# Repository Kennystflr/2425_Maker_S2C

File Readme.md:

# Sprinter Coffee Cell

Mission : Deliver Warm Coffee to the Technician on the ground level from first floor

The system includes :
- A fast RC car with a lot of cool features (might turn autonomous)
- A Lifter module.

This is a uninversitary project developed in the Maker Option at ENSEA (France).

Developed by Kenny Saint Fleur

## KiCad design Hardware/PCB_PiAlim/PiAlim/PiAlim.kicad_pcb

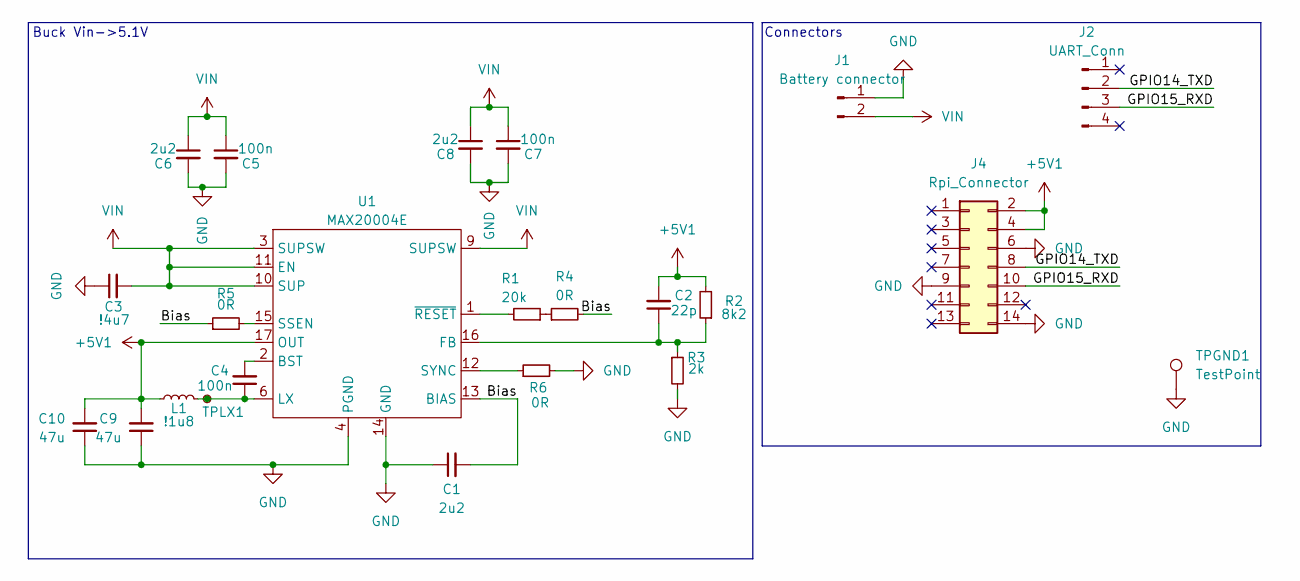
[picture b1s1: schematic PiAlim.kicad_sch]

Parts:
C1, C6, C8: 2u2; C_0805_2012Metric
C2: 22p; C_0402_1005Metric
C3: !4u7; C_0805_2012Metric; MPN UMK212BBJ475KG-T
C4, C5, C7: 100n; C_0402_1005Metric
C9, C10: 47u; C_0805_2012Metric
J1: Battery connector; AMASS_XT60-F_1x02_P7.20mm_Vertical
J2: UART_Conn; JST_XH_B4B-XH-A_1x04_P2.50mm_Vertical
J4: Rpi_Connector; PinSocket_2x07_P2.54mm_Vertical
L1: !1u8; 74437346018; MPN 74437346018
R1: 20k; R_0402_1005Metric
R2: 8k2; R_0402_1005Metric
R3: 2k; R_0402_1005Metric
R4, R5, R6: 0R; R_0402_1005Metric
TPGND1: TestPoint; TestPoint_Pad_2.0x2.0mm
TPLX1: TestPoint_Small; TestPoint_Pad_D1.0mm
U1: MAX20004E; F173A3FY+7; MPN MAX20004E

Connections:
+5V1: C2.2, C9.2, C10.2, J4.2, J4.4, L1.1, R2.2, U1.17 (OUT)
/Bias: C1.2, R4.2, R5.1, U1.13 (BIAS)
/GPIO14_TXD: J2.2, J4.8
/GPIO15_RXD: J2.3, J4.10
GND: C1.1, C3.1, C5.2, C6.2, C7.2, C8.2, C9.1, C10.1, J1.1, J4.6, J4.9, J4.14, R3.2, R6.2, TPGND1.1, U1.4 (PGND), U1.5 (PGND), U1.7 (PGND), U1.8 (PGND), U1.14 (GND)
unnamed: R1.1, R4.1
unnamed: C4.2, U1.2 (BST)
unnamed: C2.1, R2.1, R3.1, U1.16 (FB)
unnamed: C4.1, L1.2, TPLX1.1, U1.6 (LX)
unnamed: R5.2, U1.15 (SSEN)
unnamed: R6.1, U1.12 (SYNC)
unnamed: R1.2, U1.1 (~RESET)
VIN: C3.2, C5.1, C6.1, C7.1, C8.1, J1.2, U1.3 (SUPSW), U1.9 (SUPSW), U1.10 (SUP), U1.11 (EN), U1.18 (SUPSW)

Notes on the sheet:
Connectors
Buck Vin->5.1V

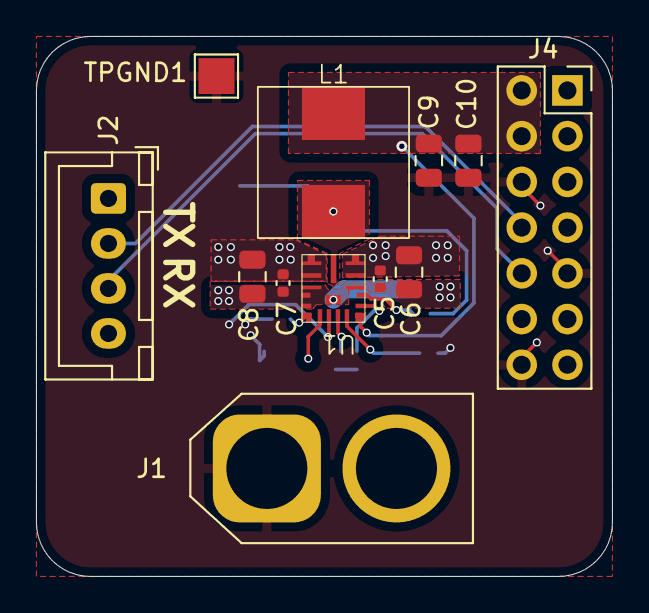
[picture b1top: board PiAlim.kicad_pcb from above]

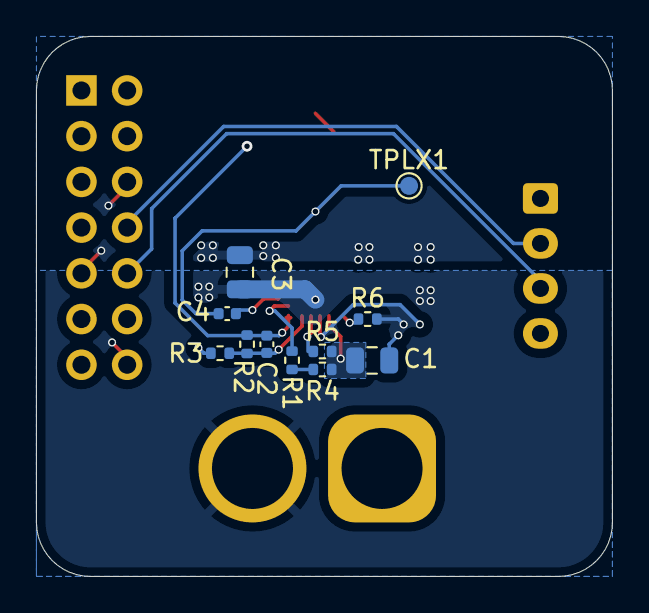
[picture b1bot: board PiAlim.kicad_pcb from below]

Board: 2 copper layers, 32.0 x 30.0 mm, 23 parts (11 on the bottom side), 13 nets.

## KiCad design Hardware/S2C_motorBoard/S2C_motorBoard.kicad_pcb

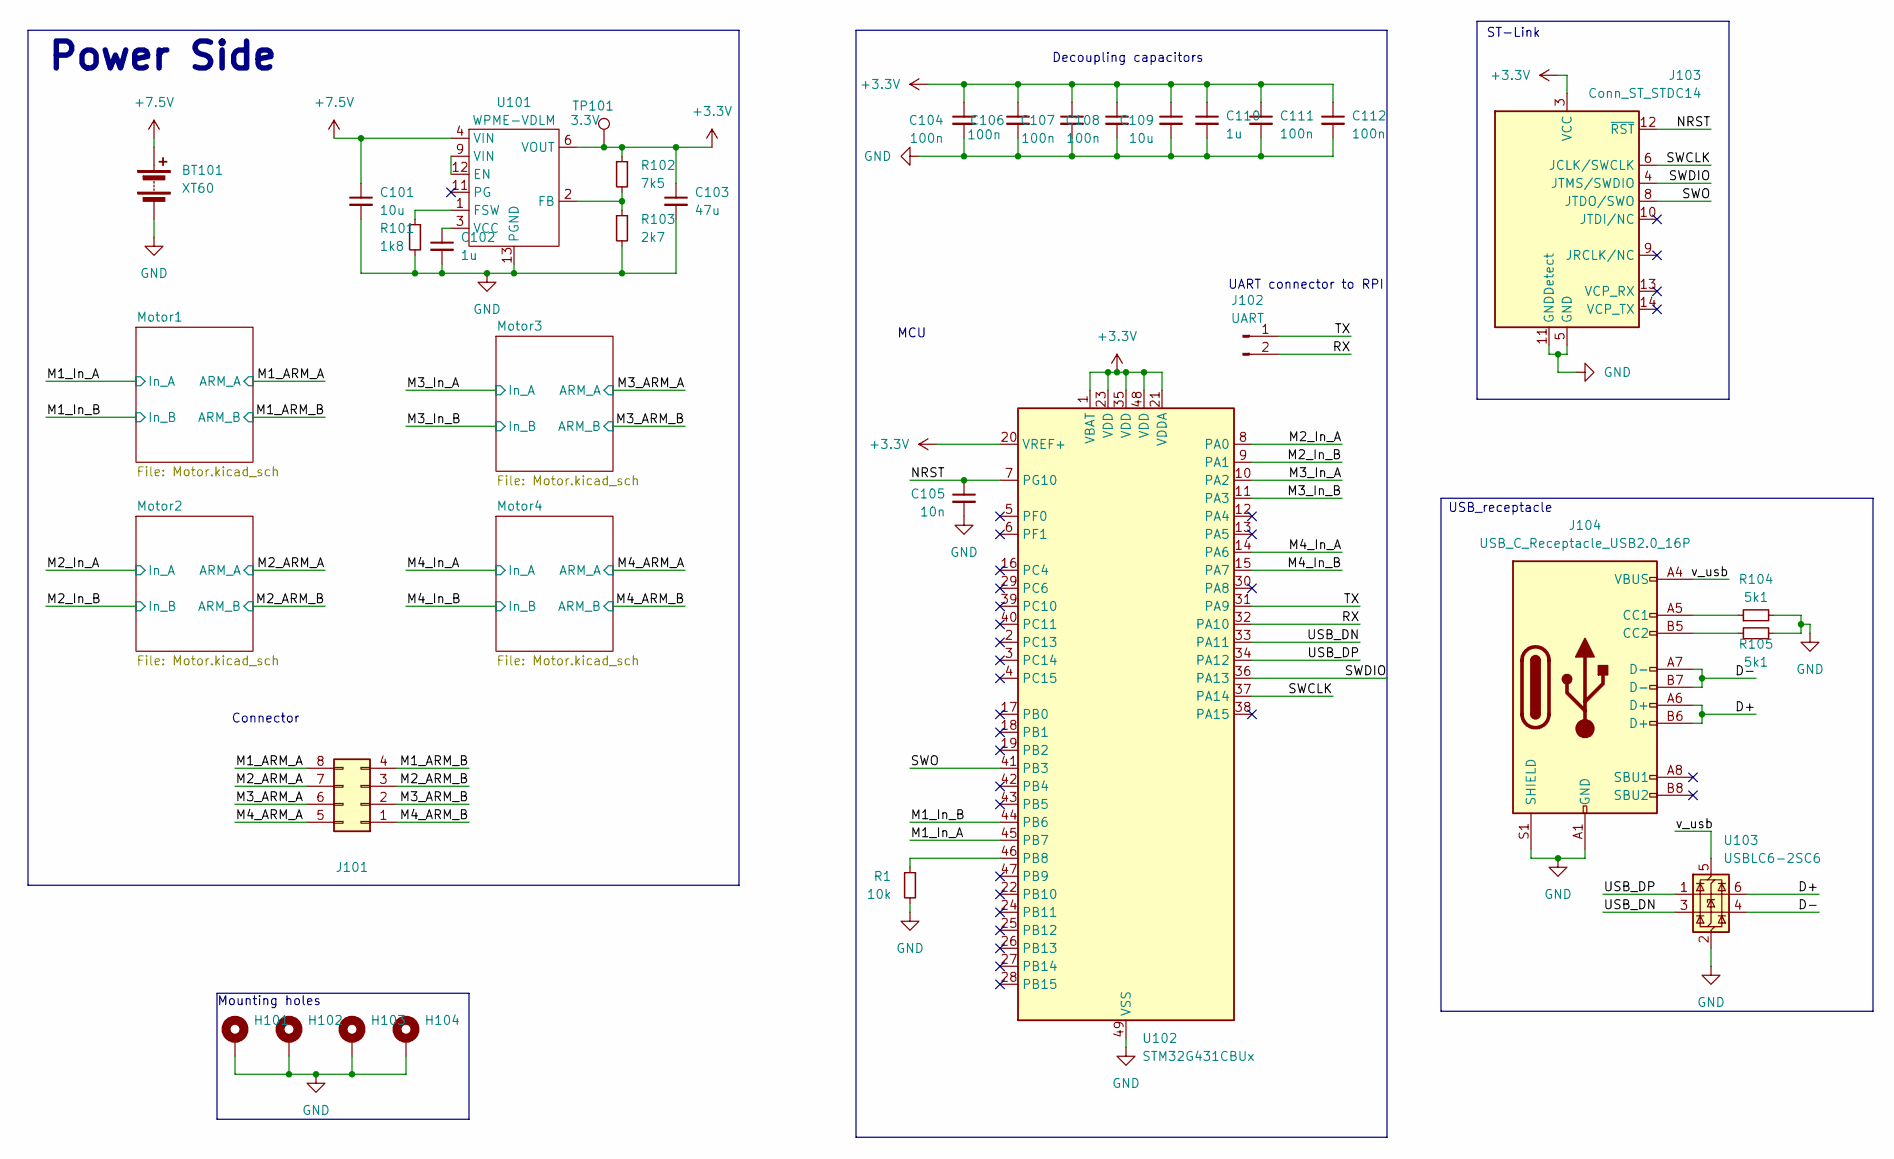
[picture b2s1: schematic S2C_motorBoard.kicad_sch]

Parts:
BT101: XT60; AMASS_XT60-M_1x02_P7.20mm_Vertical
C101: 10u; C_0805_2012Metric
C102, C110: 1u; C_0603_1608Metric
C103: 47u; C_0805_2012Metric
C104, C106, C107, C108, C111, C112: 100n; C_0402_1005Metric
C105: 10n; C_0402_1005Metric
C109: 10u; C_0603_1608Metric
H101, H102, H103, H104: MountingHole_Pad; MountingHole_2.5mm_Pad_TopBottom
J101: Conn_02x04_Odd_Even; Molex_Mini-Fit_Jr_5566-08A_2x04_P4.20mm_Vertical
J102: UART; JST_XH_B2B-XH-AM_1x02_P2.50mm_Vertical
J103: Conn_ST_STDC14; PinHeader_2x07_P1.27mm_Vertical_SMD
J104: USB_C_Receptacle_USB2.0_16P; USB_C_Receptacle_GCT_USB4105-xx-A_16P_TopMnt_Horizontal
R1: 10k; R_0402_1005Metric
R101: 1k8; R_0402_1005Metric
R102: 7k5; R_0402_1005Metric
R103: 2k7; R_0402_1005Metric
R104, R105: 5k1; R_0402_1005Metric
TP101: 3.3V; TestPoint_Pad_D2.0mm
U101: WPME-VDLM; MPN 171013801
U102: STM32G431CBUx; QFN-48-1EP_7x7mm_P0.5mm_EP5.6x5.6mm
U103: USBLC6-2SC6; SOT-23-6

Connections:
+3.3V: C103.1, C104.1, C106.1, C107.1, C108.1, C109.1, C110.1, C111.1, C112.1, J103.3 (VCC), R102.1, TP101.1, U101.6 (VOUT), U101.7 (VOUT), U102.1 (VBAT), U102.20 (VREF+), U102.21 (VDDA), U102.23 (VDD), U102.35 (VDD), U102.48 (VDD); also elsewhere on the board
+7.5V: BT101.2 (+), C101.1, U101.4 (VIN), U101.5 (VIN); also elsewhere on the board
/D+: J104.A6 (D+), J104.B6 (D+), U103.6 (I/O1)
/D-: J104.A7 (D-), J104.B7 (D-), U103.4 (I/O2)
/M1_ARM_A: J101.8; also elsewhere on the board
/M1_ARM_B: J101.4; also elsewhere on the board
/M1_In_A: U102.45 (PB7); also elsewhere on the board
/M1_In_B: U102.44 (PB6); also elsewhere on the board
/M2_ARM_A: J101.7; also elsewhere on the board
/M2_ARM_B: J101.3; also elsewhere on the board
/M2_In_A: U102.8 (PA0); also elsewhere on the board
/M2_In_B: U102.9 (PA1); also elsewhere on the board
/M3_ARM_A: J101.6; also elsewhere on the board
/M3_ARM_B: J101.2; also elsewhere on the board
/M3_In_A: U102.10 (PA2); also elsewhere on the board
/M3_In_B: U102.11 (PA3); also elsewhere on the board
/M4_ARM_A: J101.5; also elsewhere on the board
/M4_ARM_B: J101.1; also elsewhere on the board
/M4_In_A: U102.14 (PA6); also elsewhere on the board
/M4_In_B: U102.15 (PA7); also elsewhere on the board
/NRST: C105.1, J103.12 (~RST), U102.7 (PG10)
/RX: J102.2, U102.32 (PA10)
/SWCLK: J103.6 (JCLK/SWCLK), U102.37 (PA14)
/SWDIO: J103.4 (JTMS/SWDIO), U102.36 (PA13)
/SWO: J103.8 (JTDO/SWO), U102.41 (PB3)
/TX: J102.1, U102.31 (PA9)
/USB_DN: U102.33 (PA11), U103.3 (I/O2)
/USB_DP: U102.34 (PA12), U103.1 (I/O1)
/v_usb: J104.A4 (VBUS), J104.A9 (VBUS), J104.B4 (VBUS), J104.B9 (VBUS), U103.5 (VBUS)
GND: BT101.1 (-), C101.2, C102.2, C103.2, C104.2, C105.2, C106.2, C107.2, C108.2, C109.2, C110.2, C111.2, C112.2, H101.1, H102.1, H103.1, H104.1, J103.5 (GND), J103.7 (GND), J103.11 (GNDDetect), J104.A1 (GND), J104.A12 (GND), J104.B1 (GND), J104.B12 (GND), J104.S1 (SHIELD), R1.2, R101.2, R103.2, R104.2, R105.1, U101.10 (AGND), U101.13 (PGND), U102.49 (VSS), U103.2 (GND); also elsewhere on the board
unnamed: J104.A5 (CC1), R104.1
unnamed: J104.B5 (CC2), R105.2
unnamed: U101.9 (VIN), U101.12 (EN)
unnamed: R102.2, R103.1, U101.2 (FB)
unnamed: R101.1, U101.1 (FSW)
unnamed: C102.1, U101.3 (VCC)
unnamed 60: R1.1, U102.46 (PB8); also elsewhere on the board

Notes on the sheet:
Mounting holes
UART connector to RPI
MCU
USB_receptacle
Connector
ST-Link
Power Side
Decoupling capacitors

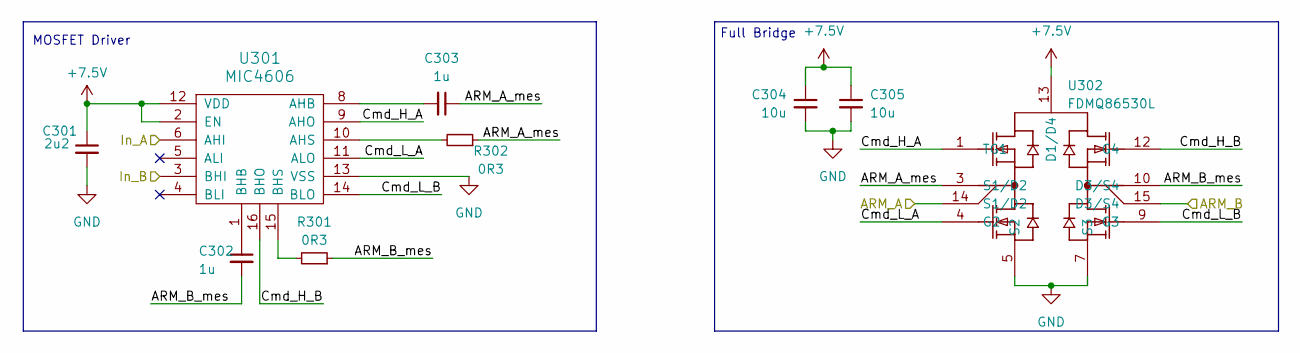
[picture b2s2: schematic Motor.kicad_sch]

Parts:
C301: 2u2; C_0603_1608Metric
C302, C303: 1u; C_0805_2012Metric
C304, C305: 10u; C_0603_1608Metric; MPN 885012106031
R301, R302: 0R3; R_1210_3225Metric
U301: MIC4606; TSSOP-16_4.4x5mm_P0.65mm
U302: FDMQ86530L

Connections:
+7.5V: C301.1, C304.1, C305.1, U301.2 (EN), U301.12 (VDD), U302.13 (D1/D4); also elsewhere on the board
/M2_ARM_A: U302.14 (S1/D2); also elsewhere on the board
/M2_ARM_B: U302.15 (D3/S4); also elsewhere on the board
/M2_In_A: U301.6 (AHI); also elsewhere on the board
/M2_In_B: U301.3 (BHI); also elsewhere on the board
/Motor2/ARM_A_mes: C303.1, R302.1, U302.3 (S1/D2)
/Motor2/ARM_B_mes: C302.2, R301.1, U302.10 (D3/S4)
/Motor2/Cmd_H_A: U301.9 (AHO), U302.1 (TG1)
/Motor2/Cmd_H_B: U301.16 (BHO), U302.12 (G4)
/Motor2/Cmd_L_A: U301.11 (ALO), U302.4 (G2)
/Motor2/Cmd_L_B: U301.14 (BLO), U302.9 (G3)
GND: C301.2, C304.2, C305.2, U301.13 (VSS), U302.5 (S2), U302.6 (PGND), U302.7 (S3), U302.8 (S3); also elsewhere on the board
unnamed: C303.2, U301.8 (AHB)
unnamed: R302.2, U301.10 (AHS)
unnamed: C302.1, U301.1 (BHB)
unnamed: R301.2, U301.15 (BHS)

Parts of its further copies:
C201, C401, C501: 2u2; C_0603_1608Metric
C202, C203, C402, C403, C502, C503: 1u; C_0805_2012Metric
C204, C205, C404, C405, C504, C505: 10u; C_0603_1608Metric; MPN 885012106031
R201, R202, R401, R402, R501, R502: 0R3; R_1210_3225Metric
U201, U401, U501: MIC4606; TSSOP-16_4.4x5mm_P0.65mm
U202, U402, U502: FDMQ86530L

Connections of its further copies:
+7.5V: C201.1, C204.1, C205.1, C401.1, C404.1, C405.1, C501.1, C504.1, C505.1, U201.2 (EN), U201.12 (VDD), U202.13 (D1/D4), U401.2 (EN), U401.12 (VDD), U402.13 (D1/D4), U501.2 (EN), U501.12 (VDD), U502.13 (D1/D4); also elsewhere on the board
/M1_ARM_A: U202.14 (S1/D2); also elsewhere on the board
/M1_ARM_B: U202.15 (D3/S4); also elsewhere on the board
/M1_In_A: U201.6 (AHI); also elsewhere on the board
/M1_In_B: U201.3 (BHI); also elsewhere on the board
/M3_ARM_A: U502.14 (S1/D2); also elsewhere on the board
/M3_ARM_B: U502.15 (D3/S4); also elsewhere on the board
/M3_In_A: U501.6 (AHI); also elsewhere on the board
/M3_In_B: U501.3 (BHI); also elsewhere on the board
/M4_ARM_A: U402.14 (S1/D2); also elsewhere on the board
/M4_ARM_B: U402.15 (D3/S4); also elsewhere on the board
/M4_In_A: U401.6 (AHI); also elsewhere on the board
/M4_In_B: U401.3 (BHI); also elsewhere on the board
/Motor1/ARM_A_mes: C203.1, R202.1, U202.3 (S1/D2)
/Motor1/ARM_B_mes: C202.2, R201.1, U202.10 (D3/S4)
/Motor1/Cmd_H_A: U201.9 (AHO), U202.1 (TG1)
/Motor1/Cmd_H_B: U201.16 (BHO), U202.12 (G4)
/Motor1/Cmd_L_A: U201.11 (ALO), U202.4 (G2)
/Motor1/Cmd_L_B: U201.14 (BLO), U202.9 (G3)
/Motor3/ARM_A_mes: C503.1, R502.1, U502.3 (S1/D2)
/Motor3/ARM_B_mes: C502.2, R501.1, U502.10 (D3/S4)
/Motor3/Cmd_H_A: U501.9 (AHO), U502.1 (TG1)
/Motor3/Cmd_H_B: U501.16 (BHO), U502.12 (G4)
/Motor3/Cmd_L_A: U501.11 (ALO), U502.4 (G2)
/Motor3/Cmd_L_B: U501.14 (BLO), U502.9 (G3)
/Motor4/ARM_A_mes: C403.1, R402.1, U402.3 (S1/D2)
/Motor4/ARM_B_mes: C402.2, R401.1, U402.10 (D3/S4)
/Motor4/Cmd_H_A: U401.9 (AHO), U402.1 (TG1)
/Motor4/Cmd_H_B: U401.16 (BHO), U402.12 (G4)
/Motor4/Cmd_L_A: U401.11 (ALO), U402.4 (G2)
/Motor4/Cmd_L_B: U401.14 (BLO), U402.9 (G3)
GND: C201.2, C204.2, C205.2, C401.2, C404.2, C405.2, C501.2, C504.2, C505.2, U201.13 (VSS), U202.5 (S2), U202.6 (PGND), U202.7 (S3), U202.8 (S3), U401.13 (VSS), U402.5 (S2), U402.6 (PGND), U402.7 (S3), U402.8 (S3), U501.13 (VSS), U502.5 (S2), U502.6 (PGND), U502.7 (S3), U502.8 (S3); also elsewhere on the board
unnamed: C203.2, U201.8 (AHB)
unnamed: R202.2, U201.10 (AHS)
unnamed: C202.1, U201.1 (BHB)
unnamed: R201.2, U201.15 (BHS)
unnamed: C403.2, U401.8 (AHB)
unnamed: R402.2, U401.10 (AHS)
unnamed: C402.1, U401.1 (BHB)
unnamed: R401.2, U401.15 (BHS)
unnamed: C503.2, U501.8 (AHB)
unnamed: R502.2, U501.10 (AHS)
unnamed: C502.1, U501.1 (BHB)
unnamed: R501.2, U501.15 (BHS)

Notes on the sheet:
Full Bridge
MOSFET Driver

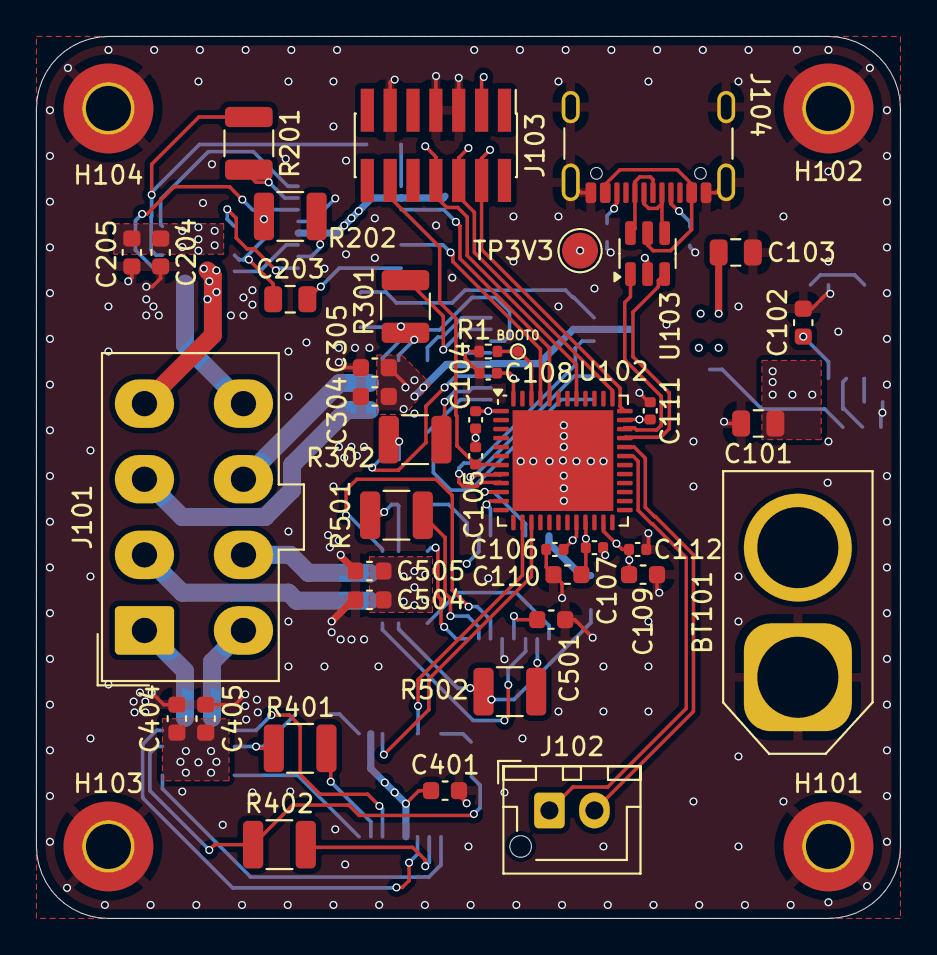
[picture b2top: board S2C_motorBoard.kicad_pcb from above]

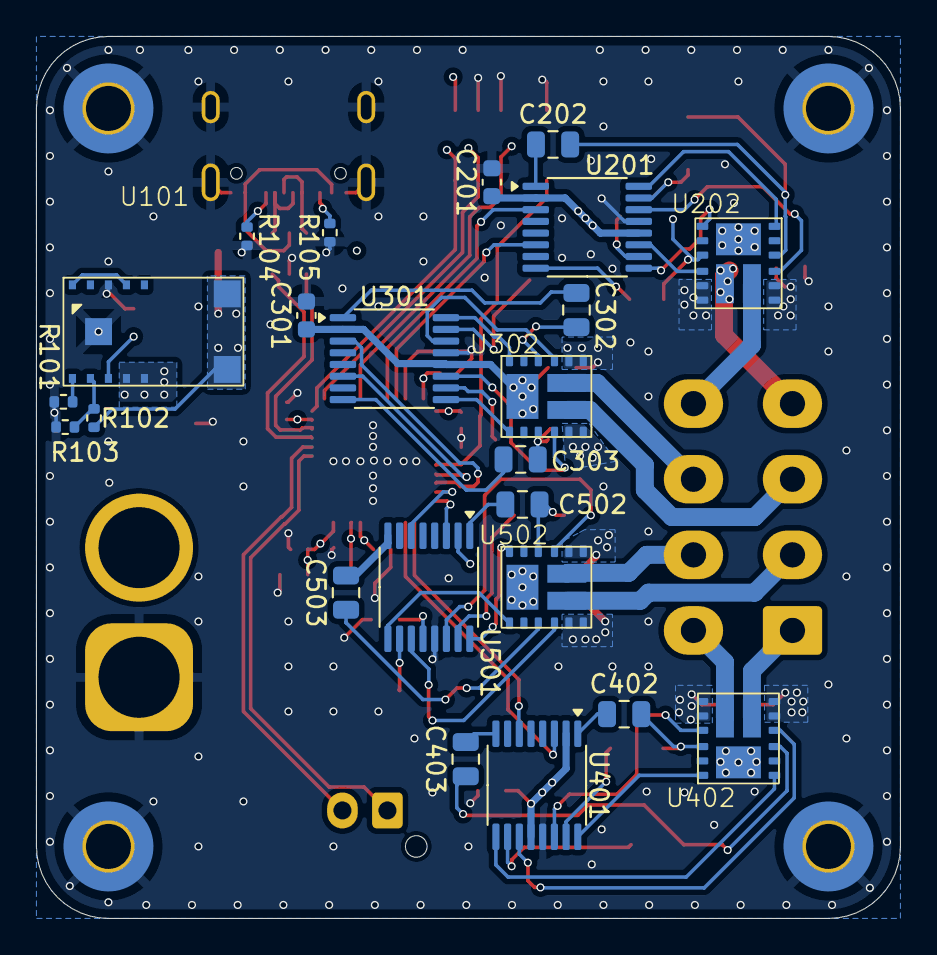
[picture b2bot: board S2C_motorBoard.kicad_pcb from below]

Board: 4 copper layers, 48.0 x 49.0 mm, 68 parts (23 on the bottom side), 77 nets.

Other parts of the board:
BOOT0: BOOT0; TestPoint_Pad_D0.5mm
TP3V3: 3.3V; TestPoint_Pad_D2.0mm

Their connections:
+3.3V: TP3V3.1; also elsewhere on the board
unnamed 60: BOOT0.1; also elsewhere on the board

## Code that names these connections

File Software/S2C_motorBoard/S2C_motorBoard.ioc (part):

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Mcu.Name=STM32G431C(6-8-B)Ux
Mcu.Package=UFQFPN48
Mcu.UserName=STM32G431CBUx
PA0.GPIOParameters=GPIO_Label
PA0.GPIO_Label=M2_A
PA0.Signal=S_TIM2_CH1
PA1.GPIOParameters=GPIO_Label
PA1.GPIO_Label=M2_B
PA1.Signal=S_TIM2_CH2
PA10.Mode=Asynchronous
PA10.Signal=USART1_RX
PA11.Mode=Device
PA11.Signal=USB_DM
PA12.Mode=Device
PA12.Signal=USB_DP
PA13.Mode=Trace_Asynchronous_SW
PA13.Signal=SYS_JTMS-SWDIO
PA14.Mode=Trace_Asynchronous_SW
PA14.Signal=SYS_JTCK-SWCLK
PA2.GPIOParameters=GPIO_Label
PA2.GPIO_Label=M3_A
PA2.Signal=S_TIM2_CH3
PA3.GPIOParameters=GPIO_Label
PA3.GPIO_Label=M3_B
PA3.Signal=S_TIM2_CH4
PA6.GPIOParameters=GPIO_Label
PA6.GPIO_Label=M1_A
PA6.Signal=S_TIM3_CH1
PA7.GPIOParameters=GPIO_Label
PA7.GPIO_Label=M1_B
PA7.Signal=S_TIM3_CH2
PA9.Mode=Asynchronous
PA9.Signal=USART1_TX
PB3.Mode=Trace_Asynchronous_SW
PB3.Signal=SYS_JTDO-SWO
PB6.GPIOParameters=GPIO_Label
PB6.GPIO_Label=M4-B
PB6.Signal=S_TIM4_CH1
PB7.GPIOParameters=GPIO_Label
PB7.GPIO_Label=M4-A
PB7.Signal=S_TIM4_CH2
RCC.HSE_VALUE=8000000
RCC.SYSCLKFreq_VALUE=100000000
RCC.SYSCLKSource=RCC_SYSCLKSOURCE_PLLCLK
board=custom

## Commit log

2025-01-16 Research
2025-01-19 Communication map
2025-02-03 PCB update
2025-02-03 adding cubeIDE project
2025-02-04 Starting with the autonomous part code
2025-02-13 PCB edits
2025-03-22 PCB Rasberry Pi Alim
2025-04-24 last pcb edits
2025-04-26 updating code
2025-04-26 updating cubeIDE
2025-04-26 code edits
